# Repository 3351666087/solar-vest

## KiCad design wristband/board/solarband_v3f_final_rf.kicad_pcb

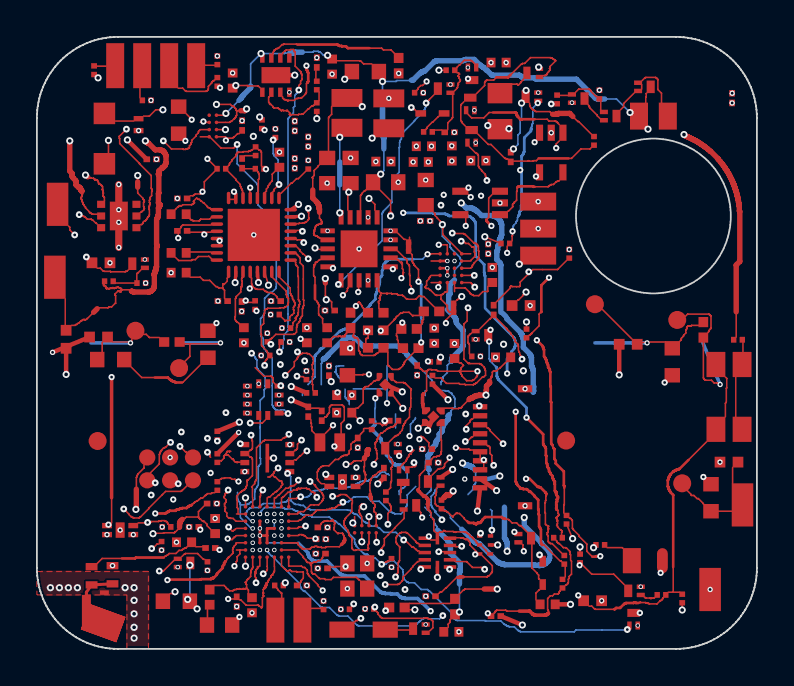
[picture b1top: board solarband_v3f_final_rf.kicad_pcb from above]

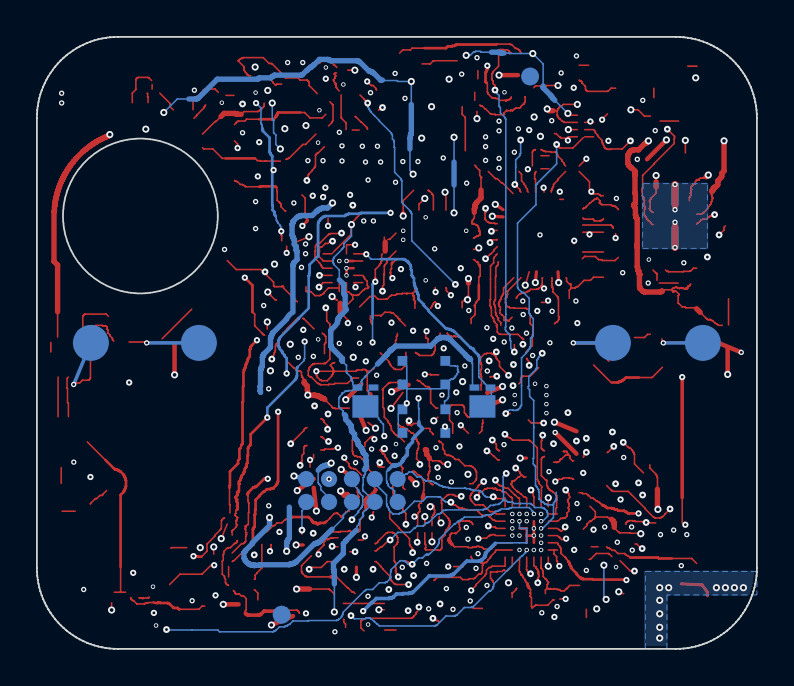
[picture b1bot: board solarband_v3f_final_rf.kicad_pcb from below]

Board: 8 copper layers, 40.0 x 34.0 mm, 242 parts (10 on the bottom side), 146 nets.

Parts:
AE1: lid strip L1 feed; AE1_lid_L1
C101: 4.7uF 16V X5R 0603; C19666_C0603
C102, C404: 10uF 10V X5R 0603; C19702_C0603
C103, C107, C108, C170, C174, C204, C205, C308, C312, C314, C401, C405, C501, C504, C505, C1503, C1601, C1602, C1603: 100nF 10V X7R 0201; C7393837_C0201
C104: 10nF 25V C0G 0402 GRM1555C1E103JE01D; C3855387_C0402
C105, C114, C115, C116, C117, C118: 22uF 6.3V X5R 0402 CL05A226MQ5QUNC; C105226_C0402
C106: 22uF 6.3V X5R 0603; C59461_C0603
C111, C112, C130, C131, C210, C309, C310, C311, C403, C1501, C1502: 1uF 25V X5R 0402; C52923_C0402
C113, C120: 10nF 25V X7R 0201; C285010_C0201
C119, C122, C313: 1uF 10V X5R 0201 GRM033R61A105ME44D; C76935_C0201
C121, C209: 4.7uF 10V X5R 0402; C23733_C0402
C132: 4.7nF 25V X7R 0201 CC0201KRX7R8BB472; C309454_C0201
C175: 220pF 5% C0G 0201 GRM0335C1H221JA01D; C161418_C0201
C201, C202: 12pF 1% C0G 0201 GRM0335C1H120FA01D; C384960_C0201
C203: 1.0pF +-0.1pF C0G 0201 GJM0335C1H1R0BB01; C237514_C0201
C206, C207: 100pF 5% C0G 0201 GRM0335C1H101JA01D; C76922_C0201
C211, C212: 20pF 5% C0G 0201 GRM0335C1H200JA01D; C76923_C0201
C213: DNP; C1546_C0402
C215: 7.6nH 0402 LQW15AN7N6G80D; C2048575_IND-SMD_L1.0-W0.6
C301, C302: DNP; C76924_C0201
C303: DNP; C76922_C0201
C304: 150pF 5% C0G 0201 GRM0335C1H151JA01D; C161408_C0201
C305, C306: 4.7nF 50V C0G 0402 GRM1555C1H472JE01D; C1518204_C0402
C307, C402, C502: 10uF 6.3V X5R 0402; C15525_C0402
D3, D4: CT DBLP31.12 green; C5603826_LED-SMD_3P-L2.2-W1.8_C5D-56-J6U6-20-R18
D5, D6, D7, D8, D15, D18: TPD1E10B06DPYR; C48260_X1SON-2_L1.0-W0.6-P0.65-BI-1
D9, D11: BAS521,115; C130414_SOD-523_L1.2-W0.8-LS1.6-RD
D10: KA-2810ASURSK hyper-red right-angle; C598214_LED-SMD_L2.5-W1.2_KA-2810AVBS-D
D12: BAV70M,315; C549313_SOT883_BAV70M_land_of_C549275
D13: ESD761DPYR; C20345399_X1SON-2_L1.0-W0.6-P0.65-BI
D14: PMEG10020AELR-QX; C6736531_SOD-123F_L2.8-W1.8-LS3.7-RD
D16: NSR0240MX2T5G; C896422_X2DFN-2_L1.0-W0.6-RD
D17, D19: BAT54CM,315; C549275_DFN1006-3_L1.0-W0.6-P0.35-BR_BAT54CM
E11, E12, E21, E22: PLATE DOT PAD 2.0 ENIG (B.Cu); Pad_PlateDot_D2.0mm
FB1, FB2, FB3, FB4, FB5, FB6: 0R 0201 0201WMF0000TEE; C473473_R0201
FID1, FID2, FID3, FID4: FIDUCIAL 1.0/2.0; Fiducial_1.0mm_Mask2.0mm
J3, J4, J5, J7, J9, J10: ROOT ENTRY PAD 1.0x2.5; Pad_RootEntry_1.0x2.5mm
J6: LID FLEX TAIL 3 x 1.0x2.0 P1.5; Pad_LidTail_3x1.0x2.0_P1.5mm
J8: POGO 2x5 P1.27 (L6); TestPad_2x5_P1.27mm_D0.9mm
J11, J15, J18, J19: BW0036BG spring finger 3.0x1.0x1.4; C2826535_SMD_L2.9-W1.0-2108613-5
J12: SWD/RESET GROUP 2x3 P1.27; TestPad_2x3_P1.27mm_D0.9mm
J13: FH34SRJ-10S-0.5SH(50); C324723_FFC-SMD_10P-P0.50_FH34SRJ-10S-0.5SH
J16: FRONT-LIGHT TAIL 2 PADS KEYED; Pad_Tail2_Keyed_FL
J17: ERM WIRE PADS 2 x 1.0x1.5; Pad_Wire2_ERM_1.0x1.5mm
J40: BW0020AG spring finger 3.5x1.5x3.0; C2826516_ANT-SMD_L3.5-W1.5-H3.8
L1: 22uH 420mA VLS201610CX-220M-1; C2050114_IND-SMD_L2.0-W1.6
L2: 10uH 550mA VLS201610CX-100M-1; C434843_IND-SMD_L2.0-W1.6
L201: 3.3nH +-0.1nH 0201 LQP03TN3N3B02D; C98045_L0201-RD
L202: 10uH 0603 MPH160809S100MT; C6807729_L0603
L203: 15nH 0402 LQG15HS15NJ02D; C86059_L0402
L204: 4.3nH 0402 LQW15AN4N3B80D; C471381_IND-SMD_L1.0-W0.6
NT1, NT2: NetTie; NetTie_2_SMD_0.3mm
PD1: VEMD8080; C511402_SENSOR-SMD_8P-L4.8-W2.5-P1.31
Q1, Q4, Q5, Q6, Q7, Q8, Q9, Q10, Q11, Q12, Q13, Q16, Q17, Q19: PMZ290UNE2YL; C478155_DFN1006-3L_L1.0-W0.6-LS1.0-BR
Q14, Q18: PMZ350UPEYL; C478207_X1-DFN1006-3_L1.0-W0.6-P0.35-BR
Q20: CJBA7002K; C504101_DFN1006-3L_L1.0-W0.6-BL
R101: 5.76M 1% 0402; C2766851_R0402
R102: 7.32M 1% 0402; C423137_R0402
R103: 3.92M 1% 0402; C423179_R0402
R104: 6.81M 1% 0402; C477775_R0402
R105: 383k 1% 0402 0402WGF3833TCE; C45993_R0402
R106: 7.5M 1% 0402; C423135_R0402
R107: 4.02M 1% 0402; C423177_R0402
R108, R125, R131, R174: 10M 1% 0201 0201WMF1005TEE; C423797_R0201
R111, R112: 1R 0.1% 25ppm 0603; C861215_R0603
R116, R165, R315, R316, R401, R402, R501, R503, R504, R509: 100k 1% 0201; C270364_R0201
R117: 3.3R 1% 0402; C270612_R0402
R123, R143: 220k 1% 0201 0201WMF2203TEE; C473458_R0201
R124, R128, R144, R145, R146, R149, R161, R163, R164, R167, R175, R176, R508, R510: 1M 1% 0201; C295786_R0201
R126: 3.3M 1% 0201 0201WMF3304TEE; C423582_R0201
R127, R505, R506: 4.7k 1% 0201; C270346_R0201
R129: 47k 1% 0201 0201WMF4702TEE; C270345_R0201
R130: 12R 1% 0805 125mW 0805W8F120JT5E; C17445_R0805
R133, R160: 100R 1% 0201 0201WMF1000TEE; C270366_R0201
R140: 10.2k 0.5% 0201 RC0201DR-0710K2L; C851635_R0201
R141: 2k 1% 0201 0201WMF2001TEE; C270358_R0201
R142: 36k 1% 0402; C43676_R0402
R162: 1k 1% 0201 0201WMF1001TEE; C270365_R0201
R170: 732k 1% 0201 0201WMF7323TEE; C423439_R0201
R171: 162k 1% 0201 0201WMF1623TEE; C2691509_R0201
R172: 53.6k 1% 0201 RTT015362FTH; C166160_R0201
R301, R302, R303, R304, R305, R306: 330k 1% 0603 ERJ-PA3 anti-surge; C441935_R0603
R307, R308, R309: DNP; C423797_R0201
R311, R312, R313, R314, R511: 10k 1% 0201; C473048_R0201
R317: 470k 1% 0201 0201WMF4703TEE; C473560_R0201
R318, R319: 100R 1% 0402; C25076_R0402
R507: 100R 1% 0402 100mW ERJ2RKF1000X; C413063_R0402
SW1: PTS840GKSMTRLFS; C221907_SW-SMD_4P-L3.5-W3.5_PTS840GKSMTRLFS
TP1, TP2, TP3, TP4, TP5: EOL TEST PAD 1.0; TestPad_D1.0mm
U1: BQ25570RGRR; C506250_VQFN-20_L3.5-W3.5-P0.50-BL-EP2.0
U3: TPS7A2030PDQNR; C5220164_X2SON-4_L1.0-W1.0-P0.65-TL-EP
U4, U5: INA236AIYBJR; C4371025_DSBGA-8_L1.5-W0.7-R2-C4-P0.40-BL
U6: nRF52832-CIAA-R; C509405_WLCSP-50_L3.2-W3.0-TL_NRF52832
U7: ADS1291IRSMR; C139059_QFN-32_L4.0-W4.0-P0.40-BL-EP2.9
U8: MAX86141ENP+T; C5328762_BGA-20_L2.0-W1.8-R4-C5-P0.40-TL
U9: LIS2DW12TR; C189624_LGA-12_L2.0-W2.0-P0.50-BL
U10: TMP117MAIDRVR; C2803242_WSON-6_L2.0-W2.0-P0.65-BL-EP
U11: MX25R1635FZUIH0; C5687033_USON-8_L3.0-W2.0-P0.50-BL-EP1.6_MX25R1635FZUIH0
U12, U13: SiP32431DNP3-T1GE4; C727398_TDFN-4_L1.2-W1.6-P0.50-BL-EP
U15: BQ25170DSGR; C5208201_WSON-8_L2.0-W2.0-P0.50-TL-EP
U16: TPS7A0230PDQNR; C2867950_UDFN-4_L1.0-W1.0-P0.65-TL
U17: TXU0104RUTR; C5187176_XQFN-12_L2.0-W1.7-P0.40-BL
U19, U20: TLV7031DCKR; C2863637_SC-70-5_L2.1-W1.3-P0.65-LS2.2-BR
U21: TXU0101DRYR; C5217869_SON-6_L1.5-W1.0-P0.50-TL
X1: 32MHz 8pF X201632MKB4SI; C718072_CRYSTAL-SMD_4P-L2.0-W1.6-BL
X2: 32.768kHz 12.5pF SC-16S; C398713_CRYSTAL-SMD_L1.6-W1.0

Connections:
ALERT_A: D10.2, R507.2
ALERT_K: D10.1, Q6.3
ALERT_LED: Q6.1, R508.1, U6.E1
ANT_FEED: AE1.1, C215.2, J40.1, L204.1
AVDD_ECG: C112.1, C311.1, C312.1, J8.10, U3.1, U7.5, U7.6, U7.12, U7.29, U7.31, U7.32
AVDD_EN: Q9.3, R123.2, U3.3
BATT_P: FB1.1, R112.2, U5.B2
BATT_P_A: FB1.2, J3.1
BQ_EN: Q4.3, R125.2, U1.5
BTN: D12.2, D18.1, R167.1, R511.1, SW1.3, SW1.4
BTN_G: Q13.1, R511.2
BTN_N: Q13.3, R164.1, U6.D3
BTN_SUP: R165.2, SW1.1, SW1.2
CHG_DIS: C175.1, Q10.1, R146.1, U6.G6
CHG_PG_N: R143.1, U6.G2, U15.6
CS_ECG: R315.1, U6.F4, U7.18
CS_FLASH: R501.1, U6.G4, U11.1
CS_PPG: R402.1, U6.H6, U8.A5
CYC_A: D11.1, R127.1
CYC_G: C122.1, Q5.1, Q7.1, R127.2, R128.1
DCC: L202.1, U6.B6
DCDC_MID: L202.2, L203.1
DEC1: C204.1, U6.B7
DEC2: C206.1, U6.A2
DEC3: C207.1, U6.C2
DEC4: C210.1, L203.2, U6.A6
DISP_CTRL: J8.6, J12.6, U6.H2, U21.3
DISP_EN: C1601.1, U6.F3, U16.3, U17.1, U17.12, U21.1, U21.5
DISP_SCS: U6.A4, U17.4
D_DISP: J13.5, U21.4
D_EXTCOMIN: J13.4, U17.7
D_SCLK: J13.1, U17.10
D_SCS: J13.3, U17.8
D_SI: J13.2, U17.9
E1_LINK: E12.1, R318.2, TP2.1
E1_MID: R301.2, R302.1
E1_PAD: D5.1, E11.1, R301.1, R318.1, TP1.1
E2_LINK: E22.1, R319.2, TP4.1
E2_MID: R305.2, R306.1
E2_PAD: D7.1, E21.1, R305.1, R319.1, TP3.1
E3_MID: R303.2, R304.1
E3_PAD: D6.1, J11.1, R303.1, TP5.1
ECG_CLK: R314.1, U7.17
ECG_DRDY: U6.E7, U7.22
ECG_GPIO1: R312.1, U7.26
ECG_GPIO2: R313.1, U7.25
ECG_INN: C302.1, C303.2, R304.2, R309.2, U7.3
ECG_INP: C301.1, C303.1, R302.2, R308.2, U7.4
ECG_PWDN: R311.1, U6.D6, U7.15
ECG_PWR_EN: R123.1, U6.F2
ECG_START: R316.1, U7.16
ECG_VCAP1: C309.1, U7.11
ECG_VCAP2: C310.1, U7.27
ECG_VREFP: C307.1, C308.1, U7.9
EN_HOLD: C121.1, D9.1, D12.3, Q4.1, R126.1
EXTCOMIN: U6.G3, U17.5
FLASH_RST: R504.1, U11.7
FLASH_WP: R503.1, U11.3
FL_A: J16.1, R160.2
FL_EN: Q11.1, R161.1, U6.G5
FL_K: J16.2, Q11.3
GK_G: Q20.3, R509.2, R510.1
GND: AE1.2, C101.2, C102.2, C103.2, C105.2, C106.2, C107.2, C108.2, C111.2, C112.2, C113.2, C114.2, C115.2, C116.2, C117.2, C118.2, C119.2, C120.2, C121.2, C122.2, C130.2, C131.2, C132.2, C170.2, C201.2, C202.2, C203.2, C204.2, C205.2, C206.2, C207.2, C209.2, C210.2, C211.2, C212.2, C213.2, C301.2, C302.2, C307.2, C308.2, C309.2, C310.2, C311.2, C312.2, C313.2, C314.2, C401.2, C402.2, C403.2, C404.2, C405.2, C501.2, C502.2, C504.2, C505.2, C1501.2, C1502.2, C1503.2, C1601.2, C1602.2, C1603.2, D5.2, D6.2, D7.2, D8.2, D13.2, D15.2, D16.2, D18.2, FB2.1, FB4.1, FB6.1, J6.2, J6.3, J8.2, J12.2, J13.9, J13.10, J13.11, J13.12, J19.1, L204.2, NT1.2, NT2.2, Q1.2, Q4.2, Q5.2, Q6.2, Q7.2, Q8.2, Q9.2, Q10.2, Q11.2, Q13.2, Q16.2, Q17.2, Q19.2, Q20.1, R108.2, R128.2, R131.2, R140.2, R142.2, R145.2, R146.2, R161.2, R163.2, R167.2, R172.2, R175.2, R176.2, R311.2, R312.2, R313.2, R314.2, R316.2, R508.2, R510.2, U1.1, U1.9, U1.15, U1.17, U1.21, U3.2, U3.5, U4.B1, U4.C2, U5.C2, U6.C4, U6.C5, U6.D2, U6.E3, U6.F5, U7.10, U7.13, U7.24, U7.33, U8.C3, U8.C4, U8.D3, U9.6, U9.7, U9.8, U10.2, U10.4, U11.4, U11.9, U12.2, U12.5, U13.2, U13.5, U15.4, U15.9, U16.2, U16.5, U17.6, U19.2, U20.2, U21.2, X1.2, X1.4
GND_A1: FB2.2, J4.1
GND_A2: FB4.2, J10.1
GND_B: FB6.2, J9.1
GND_K: D15.1, J18.1, Q20.2
GND_PMIC: C104.2, NT1.1, R101.2, R103.2, R106.2
I2C_SCL: R506.1, U4.D1, U5.D1, U6.H3, U9.1, U10.1
I2C_SDA: R505.1, U4.C1, U5.C1, U6.H4, U9.4, U10.6
IMU_INT1: U6.B3, U9.12
INA_EN: R131.1, U6.E2, U13.4
INA_VS: C107.1, C108.1, U4.D2, U5.B1, U5.D2, U13.1
ISET: R140.1, R141.1, U15.2
ISET_RC: C132.1, R141.2
LBOOST: L1.2, U1.20
LBUCK: L2.1, U1.16
LED1_DRV: D3.2, D3.3, U8.D1
LED2_DRV: D4.2, D4.3, U8.C1
MOTOR_G: Q12.1, Q19.1, R162.2, R163.1
MOTOR_N: D17.1, D17.2, J17.2, Q12.3
MOTOR_PWM: R162.1, U6.E6
MOTOR_S: Q12.2, Q19.3
NRESET: J8.5, J12.5, U6.H1
NTC: FB3.1, Q10.3, R116.2, R149.1, U15.3, U19.4, U20.3
NTC_A: FB3.2, J5.1
NTC_ADC: C113.1, R149.2, U6.A3
NTC_EN: D19.2, U6.A5
O2_G: C174.1, Q14.1, Q16.3, Q17.3, R174.1
O2_HB: C175.2, Q16.1, R176.1
O2_NC: U19.1, U20.5
O2_OK: Q17.1, R175.1, U20.1
O2_PV: D19.1, Q18.3
O2_TC: R170.2, R171.1, U19.3
O2_TH: R171.2, R172.1, U20.4
OK_HYST: R104.1, R105.2, U1.10
OK_PROG: R103.1, R104.2, U1.11
PD1_IN: PD1.1, PD1.2, PD1.3, PD1.4, PD1.6, PD1.7, PD1.8, U8.D5
PD_GND: NT2.1, PD1.5, U8.C5, U8.D4
PGA1N: C305.2, U7.1
PGA1P: C305.1, U7.2
PGA2N: C306.2, U7.7
PGA2P: C306.1, U7.8
PPG_INT: R401.1, U6.H5, U8.B2
PPG_VREF: C403.1, U8.B5
PV_INH: Q1.1, R108.1, U6.B5
PV_NODE: D8.1, FB5.1, J6.1, R111.1, R126.2, U4.A2
PV_Q: Q14.3, R130.1
PV_SW: C174.2, Q1.3, Q8.3, Q14.2, Q18.2, R111.2, R174.2, U4.B2
PV_W: FB5.2, J7.1
PWR_CYC: D11.2, U6.C6
PWR_HOLD: D9.2, U6.B4
RF_50R: C213.1, C215.1, L201.2
RF_ANT: C203.1, L201.1, U6.D1
RLD_INV: C304.1, R307.1, U7.28
RLD_OUT: R306.2, R307.2, R308.1, R309.1, R317.2, U7.30
RLD_Z: C304.2, R317.1
SPI_MISO: U6.G7, U7.21, U8.A3, U11.2
SPI_MOSI: U6.F6, U7.19, U8.A4, U11.5, U17.3
SPI_SCK: U6.F7, U7.20, U8.A2, U11.6, U17.2
SWDCLK: J8.4, J12.4, U6.F1
SWDIO: J8.3, J12.3, U6.G1
SW_ON: C120.1, R124.2, U12.4
VBAT_IC: C106.1, C131.1, D17.3, J17.1, R112.1, R125.1, R165.1, U1.18, U5.A2, U15.8
VBAT_OK: Q18.1, R129.1, U1.13
VBAT_OV: R101.1, R102.2, U1.7
VBUS: C130.1, D14.1, D16.1, R144.1, U15.1
VBUS_K: D13.1, D14.2, J15.1, R509.1
VB_DET: D12.1, Q8.1, Q9.1, R144.2, R145.1
VDD_1V8: C105.1, C114.1, C115.1, C116.1, C117.1, C205.1, C209.1, C313.1, C314.1, C401.1, C402.1, C405.1, C501.1, C502.1, C504.1, C505.1, J8.1, J12.1, L2.2, R133.1, R143.2, R164.2, R315.2, R401.2, R402.2, R501.2, R503.2, R504.2, R505.2, R506.2, U1.14, U6.A7, U6.H7, U7.14, U7.23, U8.C2, U8.D2, U9.2, U9.3, U9.9, U9.10, U10.5, U11.8, U13.3
VDD_DIS: Q7.3, R133.2
VDD_DISP: C1502.1, C1503.1, C1602.1, C1603.1, J13.6, J13.7, J13.8, U16.1, U17.11, U21.6
VIN_DC: C101.1, J8.8, L1.1, R130.2, U1.2
VLED: C118.1, C404.1, D3.1, D4.1, J8.9, R117.2, U8.A1
VOUT_EN: Q5.3, R124.1, R129.2, U1.6
VOUT_SET: R106.1, R107.2, U1.12
VRDIV: R102.1, R105.1, R107.1, U1.8
VREF_SAMP: C104.1, U1.4
VSET: R142.1, U15.7
VSTOR: C102.1, C103.1, C119.1, J8.7, U1.3, U1.19, U12.3
VSTOR_SW: C111.1, C1501.1, R117.1, R160.1, R507.1, U3.4, U12.1, U16.4
V_O2: C170.1, D19.3, R116.1, R170.1, U19.5
XC1: C201.1, U6.B2, X1.1
XC2: C202.1, U6.A1, X1.3
XL1: C211.1, U6.D7, X2.1
XL2: C212.1, U6.C7, X2.2

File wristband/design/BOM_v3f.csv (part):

Designator,Comment,Footprint,LCSC,MPN,Manufacturer,Qty,Qty_10_boards,Library,Side,Stock,Can_presale,Price_at_100_USD,Stock_risk,JLC_queried_UTC
C101,4.7uF 16V X5R 0603,easyeda_rev:C19666_C0603,C19666,CL10A475KO8NNNC,Samsung Electro-Mechanics,1,10,Basic,top,3492380,2704898,0.0112,,2026-11-15T01:31:37+00:00
"C102,C404",10uF 10V X5R 0603,easyeda_rev:C19702_C0603,C19702,CL10A106KP8NNNC,Samsung Electro-Mechanics,2,20,Basic,top,11630428,9173722,0.0233,,2026-11-15T01:31:40+00:00
"C103,C107,C108,C170,C174,C204,C205,C308,C312,C314,C401,C405,C501,C504,C505,C1503,C1601,C1602,C1603",100nF 10V X7R 0201,easyeda_rev:C7393837_C0201,C7393837,TCC0201X7R104K100ZT,CCTC,19,190,Extended,top,659227,641214,0.0019,,2026-11-15T01:34:47+00:00
C104,10nF 25V C0G 0402 GRM1555C1E103JE01D,easyeda_rev:C3855387_C0402,C3855387,GRM1555C1E103JE01D,Murata Electronics,1,10,Extended,top,65300,42401,0.0807,,2026-11-15T01:35:53+00:00
"C105,C114,C115,C116,C117",22uF 6.3V X5R 0402 CL05A226MQ5QUNC,easyeda_rev:C105226_C0402,C105226,CL05A226MQ5QUNC,Samsung Electro-Mechanics,5,50,Extended,top,170691,148186,0.1134,,2026-11-15T01:30:58+00:00
C106,22uF 6.3V X5R 0603,easyeda_rev:C59461_C0603,C59461,CL10A226MQ8NRNC,Samsung Electro-Mechanics,1,10,Basic,top,6258586,5444339,0.0221,,2026-11-15T01:34:33+00:00
"C111,C112,C130,C131,C210,C309,C310,C311,C403,C1501,C1502",1uF 25V X5R 0402,easyeda_rev:C52923_C0402,C52923,CL05A105KA5NQNC,Samsung Electro-Mechanics,11,110,Basic,top,10270857,7941064,0.0057,,2026-11-15T01:34:17+00:00
"C113,C120",10nF 25V X7R 0201,easyeda_rev:C285010_C0201,C285010,0201B103K250NT,FH (Guangdong Fenghua Advanced Tech),2,20,Extended,top,1154288,939174,0.0023,,2026-11-15T01:32:54+00:00
"C119,C122,C313",1uF 10V X5R 0201 GRM033R61A105ME44D,easyeda_rev:C76935_C0201,C76935,GRM033R61A105ME44D,Murata Electronics,3,30,Extended,top,413121,285062,0.0225,,2026-11-15T01:35:40+00:00
"C121,C209",4.7uF 10V X5R 0402,easyeda_rev:C23733_C0402,C23733,CL05A475MP5NRNC,Samsung Electro-Mechanics,2,20,Basic,top,624037,-15705,0.0113,"LOW: orderable 0 (stock 624037, canPresale -15705) < 50",2026-11-15T01:31:58+00:00
C132,4.7nF 25V X7R 0201 CC0201KRX7R8BB472,easyeda_rev:C309454_C0201,C309454,CC0201KRX7R8BB472,YAGEO,1,10,Extended,top,8124,7996,0.0038,,2026-11-15T01:35:42+00:00
C175,220pF 5% C0G 0201 GRM0335C1H221JA01D,easyeda_rev:C161418_C0201,C161418,GRM0335C1H221JA01D,Murata Electronics,1,10,Extended,top,34128,24253,0.0072,,2026-11-15T01:35:12+00:00
"C201,C202",12pF 1% C0G 0201 GRM0335C1H120FA01D,easyeda_rev:C384960_C0201,C384960,GRM0335C1H120FA01D,Murata Electronics,2,20,Extended,top,123947,114074,0.0092,,2026-11-15T01:33:05+00:00
C203,1.0pF +-0.1pF C0G 0201 GJM0335C1H1R0BB01D,easyeda_rev:C237514_C0201,C237514,GJM0335C1H1R0BB01D,Murata Electronics,1,10,Extended,top,36948,36852,0.0197,,2026-11-15T01:32:00+00:00
"C206,C207",100pF 5% C0G 0201 GRM0335C1H101JA01D,easyeda_rev:C76922_C0201,C76922,GRM0335C1H101JA01D,Murata Electronics,2,20,Extended,top,304216,265303,0.0067,,2026-11-15T01:34:50+00:00
"C211,C212",20pF 5% C0G 0201 GRM0335C1H200JA01D,easyeda_rev:C76923_C0201,C76923,GRM0335C1H200JA01D,Murata Electronics,2,20,Extended,top,9364,9194,0.0062,,2026-11-15T01:35:45+00:00
C215,7.6nH 0402 LQW15AN7N6G80D,easyeda_rev:C2048575_IND-SMD_L1.0-W0.6,C2048575,LQW15AN7N6G80D,Murata Electronics,1,10,Extended,top,6846,6810,0.0631,,2026-11-16T19:17:55+00:00
C304,150pF 5% C0G 0201 GRM0335C1H151JA01D,easyeda_rev:C161408_C0201,C161408,GRM0335C1H151JA01D,Murata Electronics,1,10,Extended,top,5980,5831,0.0121,,2026-11-15T01:35:48+00:00
"C305,C306",4.7nF 50V C0G 0402 GRM1555C1H472JE01D,easyeda_rev:C1518204_C0402,C1518204,GRM1555C1H472JE01D,Murata Electronics,2,20,Extended,top,265905,255199,0.0158,,2026-11-15T01:35:56+00:00
"C307,C402,C502",10uF 6.3V X5R 0402,easyeda_rev:C15525_C0402,C15525,CL05A106MQ5NUNC,Samsung Electro-Mechanics,3,30,Basic,top,8632077,7413577,0.0197,,2026-11-15T01:31:18+00:00
"D3,D4",CT DBLP31.12 green,easyeda_rev:C5603826_LED-SMD_3P-L2.2-W1.8_C5D-56-J6U6-20-R18,C5603826,CT DBLP31.12,OSRAM Opto Semicon,2,20,Extended,bottom,295,292,1.322,,2026-11-15T01:34:28+00:00
"D5,D6,D7,D8,D15,D18",TPD1E10B06DPYR,easyeda_rev:C48260_X1SON-2_L1.0-W0.6-P0.65-BI-1,C48260,TPD1E10B06DPYR,Texas Instruments,6,60,Extended,top,300681,298324,0.0447,,2026-11-15T12:37:06+00:00
"D9,D11","BAS521,115",easyeda_rev:C130414_SOD-523_L1.2-W0.8-LS1.6-RD,C130414,"BAS521,115",Nexperia,2,20,Extended,top,82200,81835,0.076,,2026-11-15T01:31:01+00:00
D10,KA-2810ASURSK hyper-red right-angle,easyeda_rev:C598214_LED-SMD_L2.5-W1.2_KA-2810AVBS-D,C598214,KA-2810ASURSK,Kingbright,1,10,Extended,top,1610,1610,0.2615,,2026-11-15T01:34:36+00:00
D12,"BAV70M,315",easyeda_rev:C549313_SOT883_BAV70M_land_of_C549275,C549313,"BAV70M,315",Nexperia,1,10,Extended,top,1481,1481,0.169,,2026-11-15T01:34:25+00:00
D13,ESD761DPYR,easyeda_rev:C20345399_X1SON-2_L1.0-W0.6-P0.65-BI,C20345399,ESD761DPYR,Texas Instruments,1,10,Extended,top,24136,23748,0.0989,,2026-11-15T12:37:09+00:00
D14,PMEG10020AELR-QX,easyeda_rev:C6736531_SOD-123F_L2.8-W1.8-LS3.7-RD,C6736531,PMEG10020AELR-QX,Nexperia,1,10,Extended,top,6422,6408,0.2078,,2026-11-15T12:38:37+00:00
D16,NSR0240MX2T5G,easyeda_rev:C896422_X2DFN-2_L1.0-W0.6-RD,C896422,NSR0240MX2T5G,onsemi,1,10,Extended,top,604,604,0.2607,,2026-11-15T12:54:04+00:00
"D17,D19","BAT54CM,315",easyeda_rev:C549275_DFN1006-3_L1.0-W0.6-P0.35-BR_BAT54CM,C549275,"BAT54CM,315",Nexperia,2,20,Extended,top,7036,7018,0.0745,,2026-11-15T01:34:22+00:00
"FB1,FB2,FB3,FB4,FB5,FB6",0R 0201 0201WMF0000TEE,easyeda_rev:C473473_R0201,C473473,0201WMF0000TEE,UNI-ROYAL(Uniroyal Elec),6,60,Extended,top,3405792,3062120,0.0011,,2026-11-15T01:35:37+00:00
"J11,J15,J18,J19",BW0036BG spring finger 3.0x1.0x1.4,easyeda_rev:C2826535_SMD_L2.9-W1.0-2108613-5,C2826535,BW0036BG-L3.0W1.0H1.4,BAT WIRELESS,4,40,Extended,top,6372,6367,0.0254,,2026-11-15T12:37:14+00:00
J13,FH34SRJ-10S-0.5SH(50),easyeda_rev:C324723_FFC-SMD_10P-P0.50_FH34SRJ-10S-0.5SH,C324723,FH34SRJ-10S-0.5SH(50),HRS(Hirose),1,10,Extended,top,22427,22206,0.1532,,2026-11-15T11:11:28+00:00
J40,BW0020AG spring finger 3.5x1.5x3.0,easyeda_rev:C2826516_ANT-SMD_L3.5-W1.5-H3.8,C2826518,BW0020AG-L3.5W1.5H3.0,BAT WIRELESS,1,10,Extended,top,51250,51209,0.0234,,2026-11-15T18:33:44+00:00
L1,22uH 420mA VLS201610CX-220M-1,easyeda_rev:C2050114_IND-SMD_L2.0-W1.6,C2050114,VLS201610CX-220M-1,TDK,1,10,Extended,top,3902,3853,0.0629,,2026-11-15T01:31:46+00:00
L2,10uH 550mA VLS201610CX-100M-1,easyeda_rev:C434843_IND-SMD_L2.0-W1.6,C434843,VLS201610CX-100M-1,TDK,1,10,Extended,top,6765,6730,0.0735,,2026-11-15T01:33:27+00:00
L201,3.3nH +-0.1nH 0201 LQP03TN3N3B02D,easyeda_rev:C98045_L0201-RD,C98045,LQP03TN3N3B02D,Murata Electronics,1,10,Extended,top,129031,127919,0.0128,,2026-11-15T01:35:09+00:00
L202,10uH 0603 MPH160809S100MT,easyeda_rev:C6807729_L0603,C6807729,MPH160809S100MT,Sunlord,1,10,Extended,top,46485,38833,0.0586,,2026-11-15T01:34:39+00:00
L203,15nH 0402 LQG15HS15NJ02D,easyeda_rev:C86059_L0402,C86059,LQG15HS15NJ02D,Murata Electronics,1,10,Extended,top,119564,118888,0.0252,,2026-11-15T01:35:01+00:00
L204,4.3nH 0402 LQW15AN4N3B80D,easyeda_rev:C471381_IND-SMD_L1.0-W0.6,C471381,LQW15AN4N3B80D,Murata Electronics,1,10,Extended,top,21380,21321,0.0919,,2026-11-16T19:17:59+00:00
PD1,VEMD8080,easyeda_rev:C511402_SENSOR-SMD_8P-L4.8-W2.5-P1.31,C511402,VEMD8080,Vishay Intertech,1,10,Extended,bottom,1464,1393,0.7183,,2026-11-15T01:34:00+00:00
"Q1,Q4,Q5,Q6,Q7,Q8,Q9,Q10,Q11,Q12,Q13,Q16,Q17,Q19",PMZ290UNE2YL,easyeda_rev:C478155_DFN1006-3L_L1.0-W0.6-LS1.0-BR,C478155,PMZ290UNE2YL,Nexperia,14,140,Extended,top,2271,1682,0.0392,,2026-11-15T12:37:11+00:00
"Q14,Q18",PMZ350UPEYL,easyeda_rev:C478207_X1-DFN1006-3_L1.0-W0.6-P0.35-BR,C478207,PMZ350UPEYL,Nexperia,2,20,Extended,top,21158,21105,0.0588,,2026-11-15T01:33:49+00:00
Q20,CJBA7002K,easyeda_rev:C504101_DFN1006-3L_L1.0-W0.6-BL,C504101,CJBA7002K,"Jiangsu Changjing Electronics Technology Co., Ltd.",1,10,Extended,top,6167,6162,0.0318,,2026-11-15T18:33:41+00:00
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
